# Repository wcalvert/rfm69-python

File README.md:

# rfm69-python

## Overview
This is a Python port of [Felix Rusu's RFM69 library](https://github.com/LowPowerLab/RFM69) which is a part of his Moteino project.

You will need a Beaglebone Black running a 3.8.x Linux kernel. Testing and development has been done using [Debian](>http://elinux.org/BeagleBoardDebian).

You'll need to install the [Adafruit BBIO library](https://github.com/adafruit/adafruit-beaglebone-io-python) as well.

##Status
Transmission, reception, acks, retries, encryption have been tested and seem to be working well.

##How-To
Wire up the RFM69 module first. Then clone the repository, change to the directory, and try running the included examples as root:

```
git clone https://github.com/wcalvert/rfm69-python
cd rfm69-python
su
python moteino_gateway.py
```

##Pinout
The hardware SPI module is used. The pinout is:

```
P9_1 or P9_2 = Gnd
P9_3 or P9_4 = 3.3V
P9_18 = MOSI
P9_21 = MISO
P9_22 = SCK 
P9_12 = NSS
P9_13 = DIO0 

Optional:
P9_11 = LED (Activity)
```

The chip select (NSS) and interrupt pin (DIO0) can be adjusted in rfm69.py if desired. They are just normal GPIO pins.

The LED pin (P9_11) will blink based on transmit or receive of data.

##Notes
A pullup to 3.3V on the chip select (NSS) is recommended, without it, the BBB will hang when it boots, probably due to a conflict with the SD card or something (I haven't checked the schematic to see what else is sharing that bus).

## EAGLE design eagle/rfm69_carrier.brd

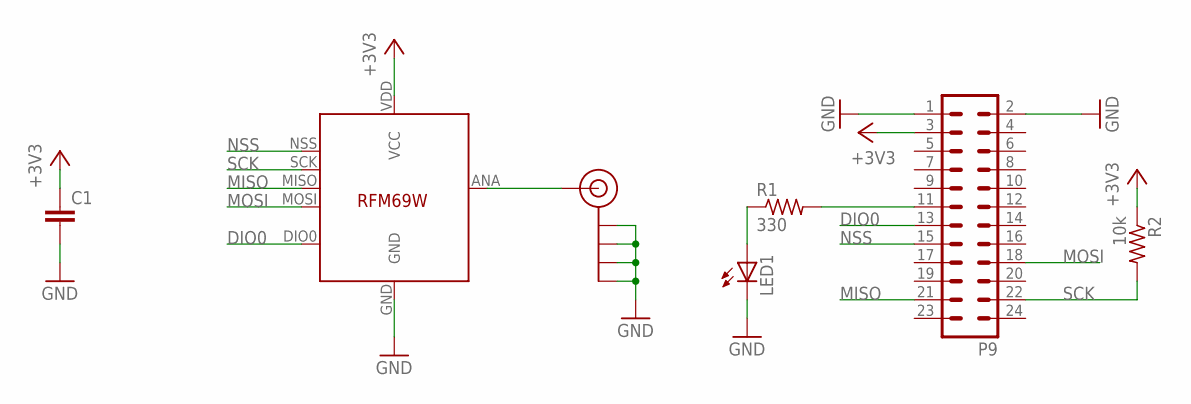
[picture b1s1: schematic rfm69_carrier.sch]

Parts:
ANT: SMA_EDGE; SMA-EDGE
C1: C-EUC1206; C1206
LED1: LEDCHIP-LED0805; CHIP-LED0805
P9: MA12-2
R1: 330; R0603
R2: 10k; R0603
U1: RFM69; RFM69W-MINPADS

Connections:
+3V3: C1.1, P9.3, R2.1, U1.VDD (VCC)
DIO0: P9.13, U1.DIO0
GND: ANT.GND@0 (GND), ANT.GND@1 (GND), ANT.GND@2 (GND), ANT.GND@3 (GND), C1.2, LED1.C, P9.1, P9.2, U1.GND
MISO: P9.21, U1.MISO
MOSI: P9.18, U1.MOSI
unnamed: ANT.SIG (SIGNAL), U1.ANA (ANT)
unnamed: P9.11, R1.2
unnamed: LED1.A, R1.1
NSS: P9.15, U1.NSS (SEL)
SCK: P9.22, R2.2, U1.SCK

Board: 2 copper layers, 7 parts (0 on the bottom side), 10 nets, no tracks yet.

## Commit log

2015-01-10 Adding files
2015-01-10 Adding readme
2015-01-10 Disable unused imports
2015-01-13 Ack fix
2015-01-13 Info update
2015-01-13 Adding Moteino node
2015-01-13 gateway cleaned up slightly
2015-01-24 Modularizing code
2015-01-24 Removing old files
2015-01-25 Adding address server stuff, mostly for backup
2015-01-28 Adding carrier board Eagle files
2015-01-28 Adding Arduino client library stuff
2015-01-28 Updated protocol
2015-01-28 Remove IDE files
2015-01-28 Remove .ds_store files
2015-02-28 Align pins in README and rfm69.py code
    Corrected pin use in rfm69.py code and added clarification for use.
    Commented out default frequency (915Mhz)
2015-02-28 Exception check for uncommented FREQUENCY
    Code to check if FREQUENCY is uncommented. If so, print and exit.
2015-03-02 Adding TCP simulator files
2015-03-03 rfm69 now inherits from base radio, some methods made 'private'
2015-03-04 Remove weird tab/space chunk
2015-03-04 Beginning to add plugins
2015-03-04 Ooops
2015-03-04 Reorganizing and cleaning up
2015-03-07 firebase plugin
2015-03-07 sms module
2015-03-07 remove underscores
2015-08-05 Half-finished work in progress...

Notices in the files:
parts and their libraries:
SparkFun-Connectors: Licensing: CC v3.0 Share-Alike You are welcome to use this library for commercial purposes.
